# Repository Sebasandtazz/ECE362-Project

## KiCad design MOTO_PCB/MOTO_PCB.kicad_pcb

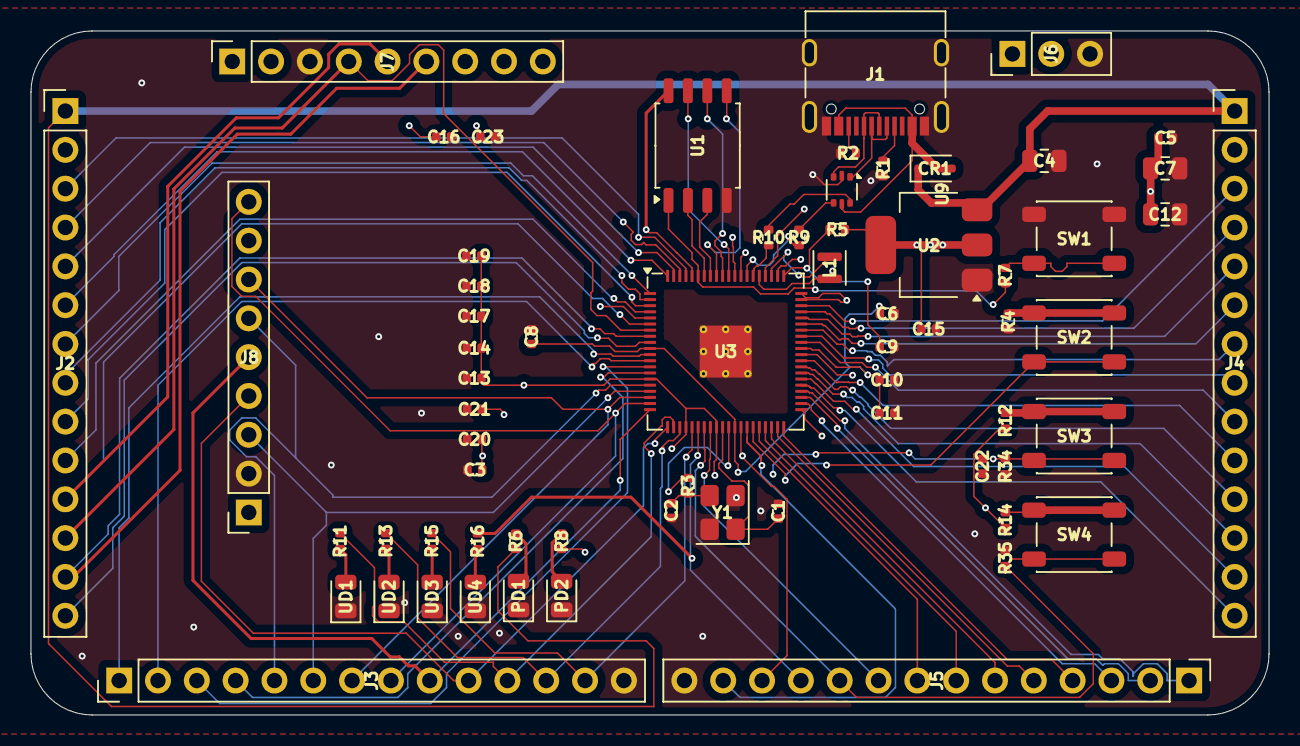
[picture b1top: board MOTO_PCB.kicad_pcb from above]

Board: 4 copper layers, 81.0 x 44.8 mm, 66 parts (0 on the bottom side), 85 nets.

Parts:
C1, C2: 15p; C_0402_1005Metric
C3, C8, C11, C13, C14, C15, C16, C17, C18, C19, C20, C21, C22, C23: 100n; C_0402_1005Metric
C4, C7, C12: 10u; C_0805_2012Metric
C5, C6, C9, C10: 4.7u; C_0402_1005Metric
CR1: BAT60JFILM; D_SOD-323F
J1: USB_C_Receptacle_USB2.0_14P; USB_C_Receptacle_G-Switch_GT-USB-7010ASV
J2, J3, J4, J5: Conn_01x14_Pin; PinHeader_1x14_P2.54mm_Vertical
J6: Conn_01x03_Pin; PinHeader_1x03_P2.54mm_Vertical
J7, J8: Conn_01x09_Socket; PinSocket_1x09_P2.54mm_Vertical
L1: 3.3u; L_Murata_DFE201610P
PD1: RED; LED_0805_2012Metric
PD2: GREEN; LED_0805_2012Metric
R1, R2, R6: 5.1k; R_0402_1005Metric
R3, R4, R7, R8, R12, R14, R15: 1k; R_0402_1005Metric
R5: 33; R_0402_1005Metric
R9, R10: 27; R_0402_1005Metric
R11: 3k; R_0402_1005Metric
R13: 2k; R_0402_1005Metric
R16: 510; R_0402_1005Metric
R34, R35: 10k; R_0402_1005Metric
SW1: BOOTSEL; SW_SPST_PTS647_Sx38
SW2: RESET; SW_SPST_PTS647_Sx38
SW3: LEFT; SW_SPST_PTS647_Sx38
SW4: RIGHT; SW_SPST_PTS647_Sx38
U1: W25Q128JVS; SOIC-8_5.3x5.3mm_P1.27mm
U2: NCP1117-3.3_SOT223; SOT-223-3_TabPin2
U3: RP2350_80QFN; QFN-80-1EP_10x10mm_P0.4mm_EP3.4x3.4mm_ThermalVias
U9: USBLC6-2P6; SOT-666
UD1: RED; LED_0805_2012Metric
UD2: YELLOW; LED_0805_2012Metric
UD3: GREEN; LED_0805_2012Metric
UD4: BLUE; LED_0805_2012Metric
Y1: ABM8-272-T3; Crystal_SMD_3225-4Pin_3.2x2.5mm

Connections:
+1V1: C6.1, C8.1, C10.1, C11.1, L1.1, U3.10 (DVDD), U3.32 (DVDD), U3.51 (DVDD), U3.65 (VREG_FB)
+3V3: C3.1, C5.1, C7.1, C12.1, C13.1, C14.1, C15.1, C16.1, C17.1, C18.1, C19.1, C20.1, C21.1, J2.2, J4.2, J7.2, J8.1, J8.8, R5.1, R8.1, R12.1, R14.1, U1.8 (VCC), U2.2 (VO), U3.5 (IOVDD), U3.15 (IOVDD), U3.24 (IOVDD), U3.29 (IOVDD), U3.41 (IOVDD), U3.50 (IOVDD), U3.59 (ADC_AVDD), U3.60 (IOVDD), U3.64 (VREG_VIN), U3.68 (USB_OTP_VDD), U3.69 (QSPI_IOVDD), U3.76 (IOVDD)
/FLASH_SS: R7.1, U1.1 (~CS), U3.75 (QSPI_SS)
/GPIO0: J2.3, U3.77 (GPIO0)
/GPIO1: J2.4, U3.78 (GPIO1)
/GPIO2: J2.5, U3.79 (GPIO2)
/GPIO3: J2.6, U3.80 (GPIO3)
/GPIO4: J2.7, U3.1 (GPIO4)
/GPIO5: J2.8, U3.2 (GPIO5)
/GPIO6: J2.9, U3.3 (GPIO6)
/GPIO7: J2.10, U3.4 (GPIO7)
/GPIO8: J2.11, J7.5, U3.6 (GPIO8)
/GPIO9: J2.12, J7.4, U3.7 (GPIO9)
/GPIO10: J2.13, J7.6, U3.8 (GPIO10)
/GPIO11: J2.14, U3.9 (GPIO11)
/GPIO12: J3.1, U3.11 (GPIO12)
/GPIO13: J3.2, U3.12 (GPIO13)
/GPIO14: J3.3, U3.13 (GPIO14)
/GPIO15: J3.4, U3.14 (GPIO15)
/GPIO16: J3.5, J8.6, U3.16 (GPIO16)
/GPIO17: J3.6, J8.3, U3.17 (GPIO17)
/GPIO18: J3.7, J8.7, U3.18 (GPIO18)
/GPIO19: J3.8, J8.9, U3.19 (GPIO19)
/GPIO20: J3.9, J8.5, U3.20 (GPIO20)
/GPIO21: C22.1, J3.10, J8.4, R34.2, SW3.2, U3.21 (GPIO21)
/GPIO22: J3.11, R11.1, U3.22 (GPIO22)
/GPIO23: J3.12, R13.1, U3.23 (GPIO23)
/GPIO24: J3.13, R15.1, U3.25 (GPIO24)
/GPIO25: J5.11, R16.1, U3.26 (GPIO25)
/GPIO26: C23.1, J5.10, R35.2, SW4.2, U3.27 (GPIO26)
/GPIO27: J5.9, U3.28 (GPIO27)
/GPIO28: J5.8, U3.36 (GPIO28)
/GPIO29: J5.7, U3.37 (GPIO29)
/GPIO30: J5.6, U3.38 (GPIO30)
/GPIO31: J5.5, U3.39 (GPIO31)
/GPIO32: J5.4, U3.40 (GPIO32)
/GPIO33: J5.3, U3.42 (GPIO33)
/GPIO34: J5.2, U3.43 (GPIO34)
/GPIO35: J5.1, U3.44 (GPIO35)
/GPIO36: J4.14, U3.45 (GPIO36)
/GPIO37: J4.13, U3.46 (GPIO37)
/GPIO38: J4.12, U3.47 (GPIO38)
/GPIO39: J4.11, U3.48 (GPIO39)
/GPIO40_ADC0: J4.10, U3.49 (GPIO40_ADC0)
/GPIO41_ADC1: J4.9, U3.52 (GPIO41_ADC1)
/GPIO42_ADC2: J4.8, U3.53 (GPIO42_ADC2)
/GPIO43_ADC3: J4.7, U3.54 (GPIO43_ADC3)
/GPIO44_ADC4: J4.6, U3.55 (GPIO44_ADC4)
/GPIO45_ADC5: J4.5, U3.56 (GPIO45_ADC5)
/GPIO46_ADC6: J4.4, U3.57 (GPIO46_ADC6)
/GPIO47_ADC7: J4.3, U3.58 (GPIO47_ADC7)
/QSPI_SCLK: U1.6 (CLK), U3.71 (QSPI_SCLK)
/QSPI_SD0: U1.5 (DI(IO0)), U3.72 (QSPI_SD0)
/QSPI_SD1: U1.2 (DO(IO1)), U3.74 (QSPI_SD1)
/QSPI_SD2: U1.3 (IO2), U3.73 (QSPI_SD2)
/QSPI_SD3: U1.7 (IO3), U3.70 (QSPI_SD3)
/RUN: SW2.2, U3.35 (RUN)
/SWCLK: J5.12, J6.1, U3.33 (SWCLK)
/SWD: J5.13, J6.2, U3.34 (SWD)
/USB_D+: R9.1, U9.4 (I/O2)
/USB_D-: R10.1, U9.6 (I/O1)
/VREG_AVDD: C9.1, R5.2, U3.61 (VREG_AVDD)
/VREG_LX: L1.2, U3.63 (VREG_LX)
/XIN: C1.1, U3.30 (XIN), Y1.1
/XOUT: R3.1, U3.31 (XOUT)
/~USB_BOOT: R7.2, SW1.2
GND: C1.2, C2.2, C3.2, C4.2, C5.2, C6.2, C7.2, C8.2, C9.2, C10.2, C11.2, C12.2, C13.2, C14.2, C15.2, C16.2, C17.2, C18.2, C19.2, C20.2, C21.2, C22.2, C23.2, J1.A1 (GND), J1.A12 (GND), J1.B1 (GND), J1.B12 (GND), J1.S1 (SHIELD), J3.14, J5.14, J6.3, J7.3, J8.2, PD1.1 (K), PD2.1 (K), R1.2, R2.2, R4.2, R34.1, R35.1, SW1.1, U1.4 (GND), U2.1 (GND), U3.62 (VREG_PGND), U3.81 (GND), U9.2 (GND), UD1.1 (K), UD2.1 (K), UD3.1 (K), UD4.1 (K), Y1.2, Y1.4
unnamed: C2.1, R3.2, Y1.3
unnamed: J1.A5 (CC1), R1.1
unnamed: J1.B5 (CC2), R2.1
unnamed: J1.A6 (D+), J1.B6 (D+), U9.3 (I/O2)
unnamed: J1.A7 (D-), J1.B7 (D-), U9.1 (I/O1)
unnamed: PD1.2 (A), R6.2
unnamed: PD2.2 (A), R8.2
unnamed: R4.1, SW2.1
unnamed: R12.2, SW3.1
unnamed: R14.2, SW4.1
unnamed: R10.2, U3.66 (USB_DM)
unnamed: R9.2, U3.67 (USB_DP)
unnamed: R11.2, UD1.2 (A)
unnamed: R13.2, UD2.2 (A)
unnamed: R15.2, UD3.2 (A)
unnamed: R16.2, UD4.2 (A)
UVBUS: CR1.2, J1.A4 (VBUS), J1.A9 (VBUS), J1.B4 (VBUS), J1.B9 (VBUS), U9.5 (VBUS)
VBUS: C4.1, CR1.1, J2.1, J4.1, R6.1, U2.3 (VI)

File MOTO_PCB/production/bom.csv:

Designator,Footprint,Quantity,Value,LCSC Part #
"C1, C2",0402,2,15p,
"C10, C5, C6, C9",0402,4,4.7u,
"C11, C13, C14, C15, C16, C17, C18, C19, C20, C21, C22, C23, C3, C8",0402,14,100n,
"C12, C4, C7",0805,3,10u,
CR1,D_SOD-323F,1,BAT60JFILM,
J1,USB_C_Receptacle_G-Switch_GT-USB-7010ASV,1,USB_C_Receptacle_USB2.0_14P,
"J2, J3, J4, J5",PinHeader_1x14_P2.54mm_Vertical,4,Conn_01x14_Pin,
J6,PinHeader_1x03_P2.54mm_Vertical,1,Conn_01x03_Pin,
"J7, J8",PinSocket_1x09_P2.54mm_Vertical,2,Conn_01x09_Socket,
L1,L_Murata_DFE201610P,1,3.3u,
"PD1, UD1",0805,2,RED,
"PD2, UD3",0805,2,GREEN,
"R1, R2, R6",0402,3,5.1k,
"R10, R9",0402,2,27,
R11,0402,1,3k,
"R12, R14, R15, R3, R4, R7, R8",0402,7,1k,
R13,0402,1,2k,
R16,0402,1,510,
"R34, R35",0402,2,10k,
R5,0402,1,33,
SW1,SW_SPST_PTS647_Sx38,1,BOOTSEL,
SW2,SW_SPST_PTS647_Sx38,1,RESET,
SW3,SW_SPST_PTS647_Sx38,1,LEFT,
SW4,SW_SPST_PTS647_Sx38,1,RIGHT,
U1,SOIC-8_5.3x5.3mm_P1.27mm,1,W25Q128JVS,
U2,SOT-223-3_TabPin2,1,NCP1117-3.3_SOT223,
U3,QFN-80-1EP_10x10mm_P0.4mm_EP3.4x3.4mm_ThermalVias,1,RP2350_80QFN,
U9,SOT-666,1,USBLC6-2P6,
UD2,0805,1,YELLOW,
UD4,0805,1,BLUE,
Y1,Crystal_SMD_3225-4Pin_3.2x2.5mm,1,ABM8-272-T3,

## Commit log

2025-11-03 Initial repo for all project files, all board files should be added seperately.
2025-11-04 added header
2025-11-11 Added library will build?
2025-11-11 Added the library back, still seems like ?
2025-11-11 Adding PCB
2025-11-17 starting with custom GPS code
2025-11-19 Should all be pushed
2025-11-19 LCD Initial Code
2025-11-19 Beuh
2025-11-19 Merged GPS and TFT data
2025-11-19 Should all be correct?
2025-11-19 LCD States
2025-11-21 More routing
2025-11-21 Better
2025-11-21 More Vias
2025-11-21 More line!
2025-11-30 Updating Display Functions
2025-11-30 Updated Variable Type
2025-12-01 Added parsing
2025-12-01 Dumb stupid variable name shoot me
2025-12-01 add page disp
2025-12-01 Null STRTOk
2025-12-01 Fixed?
2025-12-01 PWM stuff
2025-12-03 Updated Lat Lon Disp
2025-12-03 Updated Disp Time
2025-12-03 Updated Disp Speed
2025-12-03 Updated Disp Location
2025-12-03 WORKING PARSING!!
2025-12-03 Added Drawing Functions
2025-12-04 yay!
2025-12-04 Updated Display Code
2025-12-04 horses don't stop.
